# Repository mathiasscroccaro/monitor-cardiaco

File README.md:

# monitor-cardiaco
Códigos fonte da interface de visualização do sinal, instruções programadas no microcontrolador e também esquemáticos dos circuitos do protótipo de monitor cardíaco

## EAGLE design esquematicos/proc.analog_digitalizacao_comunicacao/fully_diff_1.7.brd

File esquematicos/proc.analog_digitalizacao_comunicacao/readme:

Arquivos do esquemático da placa de processamento analógico, digitalização e comunicação do protótipo de monitor cardíaco

Os esquemáticos presentes neste diretórios são compatíveis com o software EDA Eagle

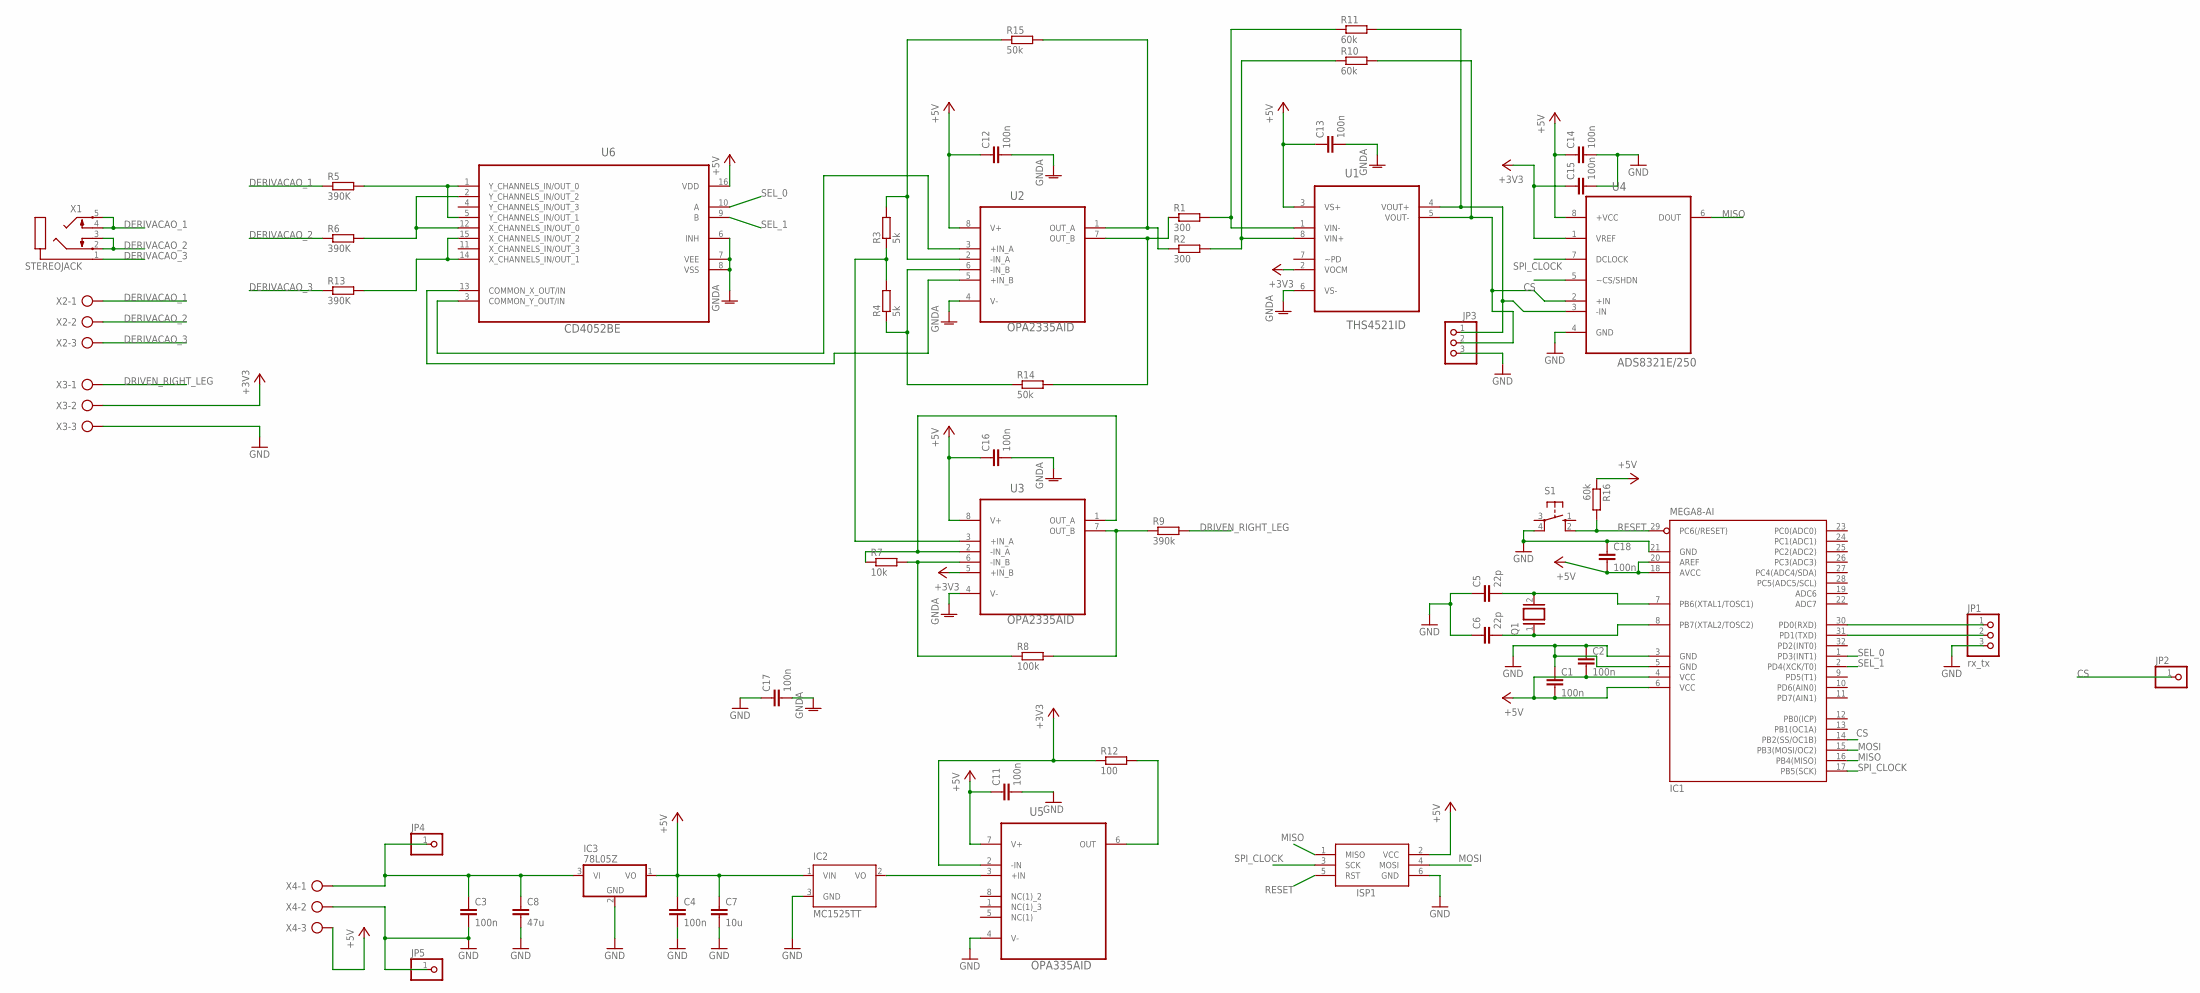
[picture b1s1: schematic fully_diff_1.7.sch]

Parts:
C1, C2, C3, C4, C11, C12, C13, C14, C15, C16, C17, C18: 100n; C1206
C5, C6: 22p; C1206
C7: 10u; C025-030X050
C8: 47u; C025-030X050
IC1: MEGA8-AI; TQFP32-08
IC2: MC1525TT; SOT23
IC3: 78L05Z; TO92
ISP1: AVRISP-6; AVRISP
JP1: rx_tx; 1X03
JP2, JP4, JP5: PINHD-1X1; 1X01
JP3: PINHD-1X3; 1X03
Q1: XTAL/S; QS
R1, R2: 300; R1206
R3, R4: 5k; R1206
R5, R6, R13: 390K; R1206
R7: 10k; R1206
R8: 100k; R1206
R9: 390k; R1206
R10, R11, R16: 60k; R1206
R12: 100; R1206
R14, R15: 50k; R1206
S1: 10-XX; B3F-10XX
U1: THS4521ID; SOIC127P600X175-8N
U2, U3: OPA2335AID; SOIC127P600X175-8N
U4: ADS8321E/250; SOP65P490X110-8N
U5: OPA335AID; SOIC127P600X175-8N
U6: CD4052BE; DIP254P762X508-16
X1: STEREOJACK; STX3100
X2, X3, X4: AK300/3

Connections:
+3V3: C15.1, R12.1, U1.2 (VOCM), U3.5 (+IN_B), U4.1 (VREF), U5.2 (-IN), X3.2
+5V: C1.2, C2.2, C4.1, C7.1, C11.1, C12.1, C13.1, C14.1, C16.1, C18.2, IC1.4 (VCC), IC1.6 (VCC), IC1.18 (AVCC), IC1.20 (AREF), IC2.1 (VIN), IC3.1 (VO), ISP1.2 (VCC), R16.1, U1.3 (VS+), U2.8 (V+), U3.8 (V+), U4.8 (+VCC), U5.7 (V+), U6.16 (VDD), X4.3
CS: IC1.14 (PB2(SS/OC1B)), JP2.1, U4.5 (~CS/SHDN)
DERIVACAO_1: R5.1, X1.4, X1.5, X2.1
DERIVACAO_2: R6.1, X1.2, X1.3, X2.2
DERIVACAO_3: R13.1, X1.1, X2.3
DRIVEN_RIGHT_LEG: R9.2, X3.1
GND: C1.1, C2.1, C3.2, C4.2, C5.1, C6.1, C7.2, C8.2, C11.2, C14.2, C15.2, C17.1, C18.1, IC1.3 (GND), IC1.5 (GND), IC1.21 (GND), IC2.3 (GND), IC3.2 (GND), ISP1.6 (GND), JP1.3, JP3.3, JP5.1, S1.4 (P1), U4.4 (GND), U5.4 (V-), X3.3, X4.2
GNDA: C12.2, C13.2, C16.2, C17.2, U1.6 (VS-), U2.4 (V-), U3.4 (V-), U6.6 (INH), U6.7 (VEE), U6.8 (VSS)
MISO: IC1.16 (PB4(MISO)), ISP1.1 (MISO), U4.6 (DOUT)
MOSI: IC1.15 (PB3(MOSI/OC2)), ISP1.4 (MOSI)
unnamed: R2.2, R10.1, U1.8 (VIN+)
unnamed: R1.2, R11.1, U1.1 (VIN-)
unnamed: R1.1, R14.2, U2.7 (OUT_B)
unnamed: R2.1, R15.2, U2.1 (OUT_A)
unnamed: R3.2, R15.1, U2.2 (-IN_A)
unnamed: R4.1, R14.1, U2.6 (-IN_B)
unnamed: R3.1, R4.2, U3.3 (+IN_A)
unnamed: R6.2, U6.2 (Y_CHANNELS_IN/OUT_2), U6.12 (X_CHANNELS_IN/OUT_0)
unnamed: R7.1, U3.1 (OUT_A), U3.2 (-IN_A)
unnamed: R8.2, R9.1, U3.7 (OUT_B)
unnamed: R7.2, R8.1, U3.6 (-IN_B)
unnamed: JP3.2, R10.2, U1.5 (VOUT-), U4.2 (+IN)
unnamed: JP3.1, R11.2, U1.4 (VOUT+), U4.3 (-IN)
unnamed: C5.2, IC1.7 (PB6(XTAL1/TOSC1)), Q1.2
unnamed: U2.5 (+IN_B), U6.13 (COMMON_X_OUT/IN)
unnamed: U2.3 (+IN_A), U6.3 (COMMON_Y_OUT/IN)
unnamed: IC2.2 (VO), U5.3 (+IN)
unnamed: C6.2, IC1.8 (PB7(XTAL2/TOSC2)), Q1.1
unnamed: R5.2, U6.1 (Y_CHANNELS_IN/OUT_0), U6.5 (Y_CHANNELS_IN/OUT_1)
unnamed: R12.2, U5.6 (OUT)
unnamed: IC1.30 (PD0(RXD)), JP1.1
unnamed: R13.2, U6.14 (X_CHANNELS_IN/OUT_1), U6.15 (X_CHANNELS_IN/OUT_2)
unnamed: C3.1, C8.1, IC3.3 (VI), JP4.1, X4.1
unnamed: IC1.31 (PD1(TXD)), JP1.2
RESET: IC1.29 (PC6(/RESET)), ISP1.5 (RST), R16.2, S1.2 (S1)
SEL_0: IC1.1 (PD3(INT1)), U6.10 (A)
SEL_1: IC1.2 (PD4(XCK/T0)), U6.9 (B)
SPI_CLOCK: IC1.17 (PB5(SCK)), ISP1.3 (SCK), U4.7 (DCLOCK)

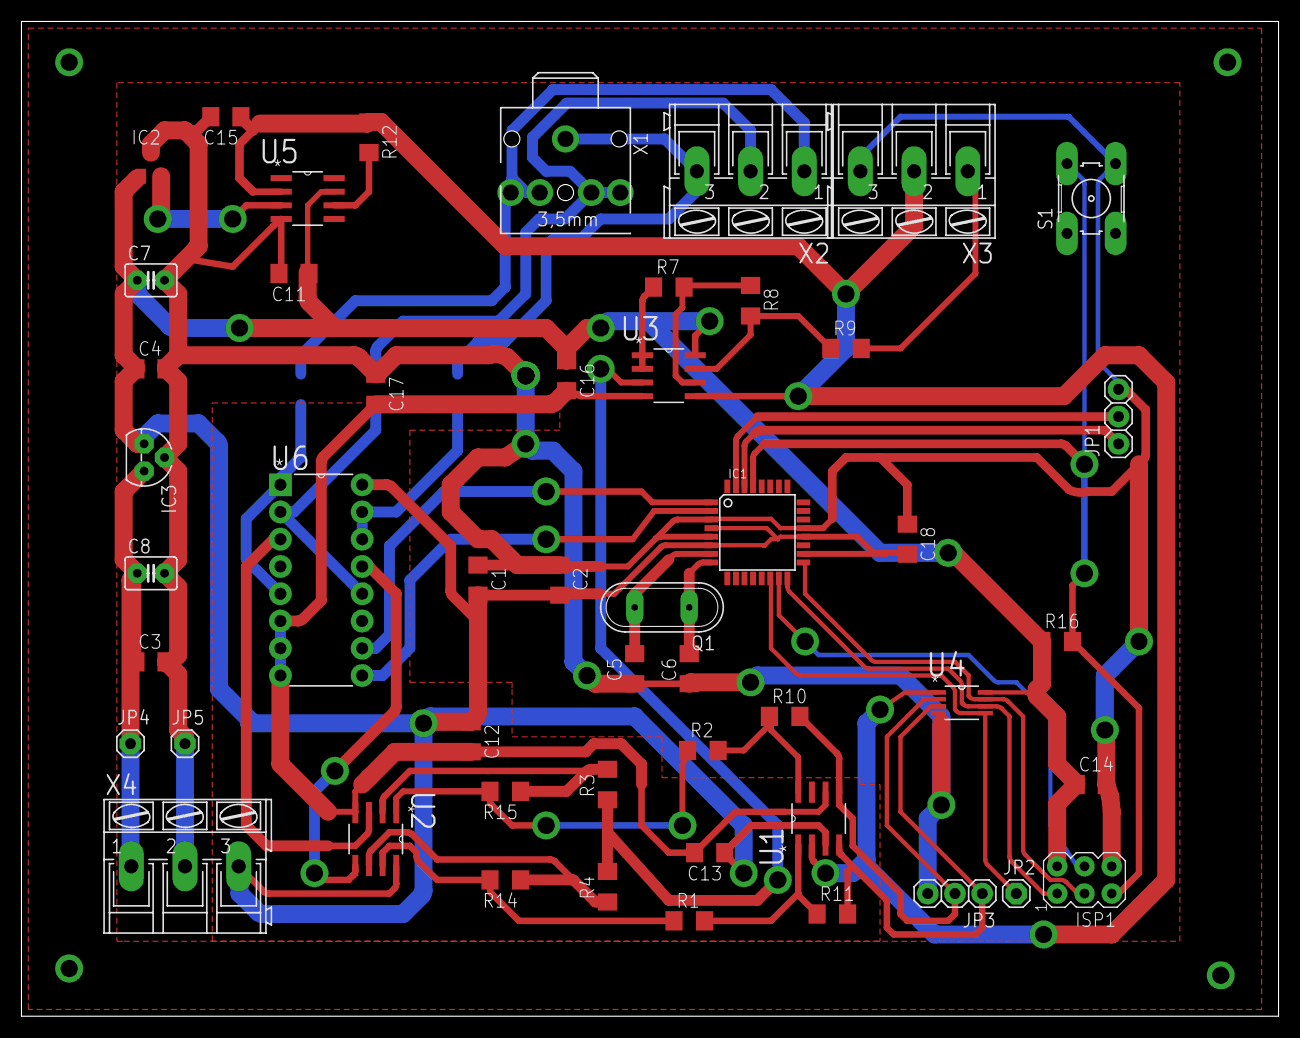
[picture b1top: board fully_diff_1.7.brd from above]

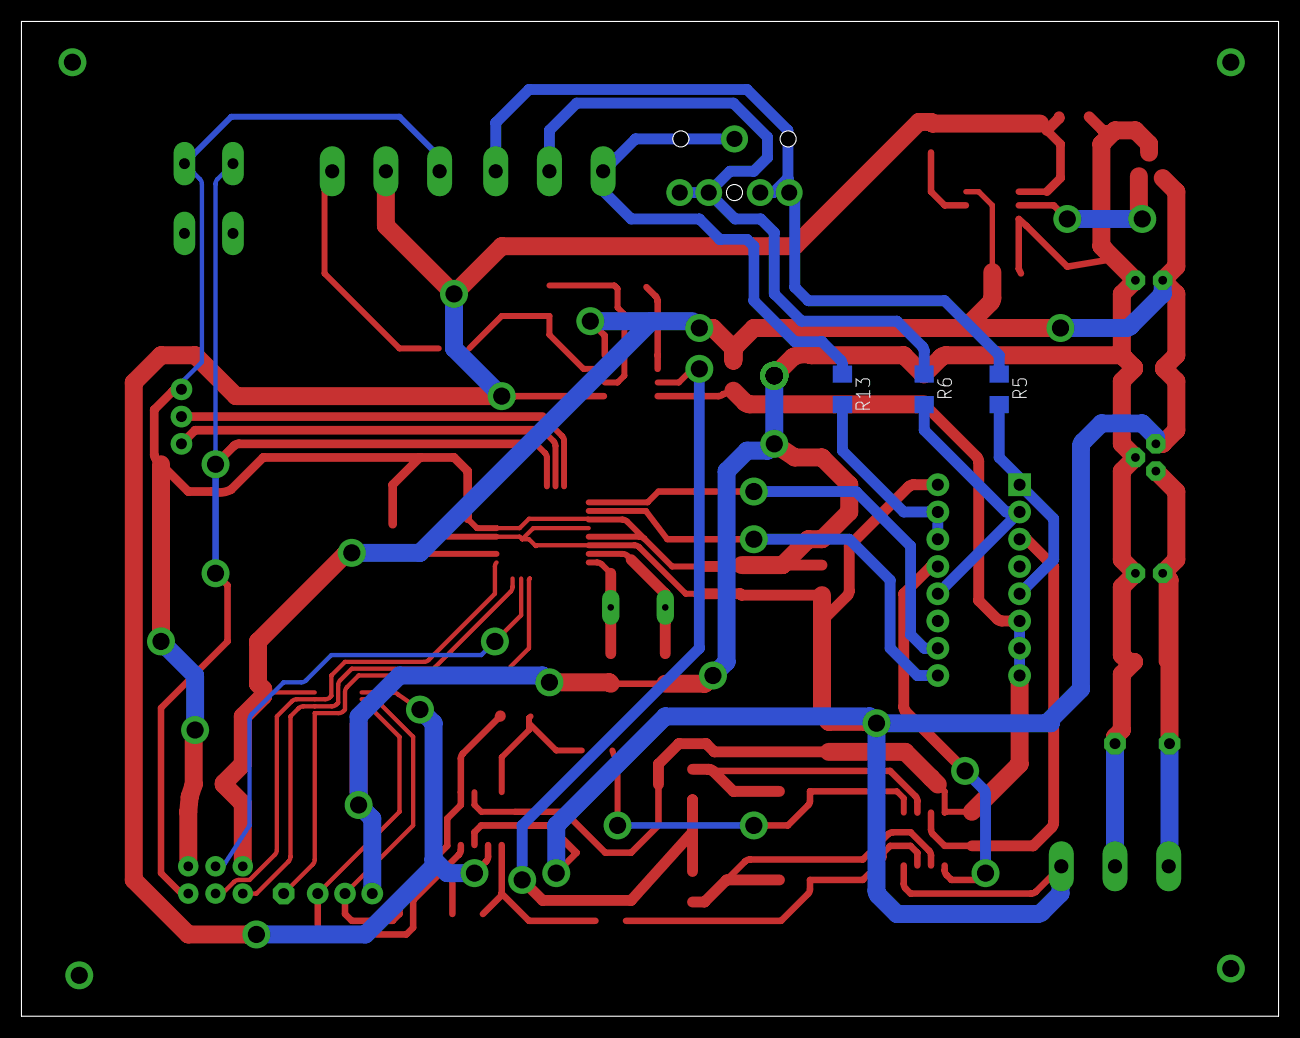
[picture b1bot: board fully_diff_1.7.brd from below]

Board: 2 copper layers, 117.1 x 92.7 mm, 53 parts (3 on the bottom side), 39 nets.
